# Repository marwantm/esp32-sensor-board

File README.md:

# ESP32 Sensor Board

A 4-layer ESP32-C3 IoT sensor board with onboard LiPo charging, SD storage, and a multi-sensor front end, designed in KiCad by following Tech Explorations' full board-development pipeline tutorial — my most advanced build yet, covering the complete flow from schematic to manufacturing and assembly.

## Overview

This board is built around the **ESP32-C3-WROOM-02**, a RISC-V Wi-Fi/BLE module, paired with a small sensor suite (environmental, audio, and light), onboard SPI flash, microSD storage, and a full LiPo battery charging path — a compact, self-contained IoT sensor node platform.

| | |
|---|---|
| **MCU** | ESP32-C3-WROOM-02 (RISC-V, Wi-Fi + BLE) |
| **Sensors** | BME280 (temperature/humidity/pressure), electret mic + MAX4466 amplifier, TEMT6000 ambient light sensor |
| **Storage** | W25Q32JVSSIQ SPI flash (32 Mbit) + microSD card slot |
| **Connectivity** | USB-C (via CP2102N USB-UART bridge), I2C header for OLED display, GPIO breakout |
| **Power** | USB-C (5V) or LiPo battery (JST connector), MCP73871 Li-ion/LiPo charge management, LM1117MPX-3.3 LDO |
| **Programming** | Auto-program circuit (DTR/RTS → EN/IO0 via BC817 transistors) — no manual boot/reset sequence needed |
| **PCB** | 4-layer |
| **Design Tool** | KiCad 9 |

## What I Learned

This project pushed further than my previous boards, moving from single-sheet schematics and simple 2-layer boards into a full multilayer design with manufacturing and assembly considerations built in from the start:

**Schematic Design**
- Multi-sheet hierarchical schematic structure, splitting the design into logical sub-sheets (USB/flash, sensors, user interface, power)
- Creating a custom KiCad component library for parts not available in the standard libraries, registered globally for reuse in future projects
- Designing a complete LiPo charging path around the MCP73871, including charge-status indication (charging/charged LEDs) and battery sense/thermistor handling

**PCB Layout**
- Working with a 4-layer stack-up and signal tuning across layers
- Zone fills across both available and non-available power planes, and understanding how that affects plane continuity and return paths
- Component placement and routing for mixed digital, analog (microphone/amp), and RF (Wi-Fi/BLE) sections on the same board

**Manufacturing & Assembly**
- Design for Manufacturability (DFM) checks using HQDFM (NextPCB)
- Generating centroid (pick-and-place) files for PCB assembly
- Thinking through the board as something meant to be assembled by a fab, not just etched and hand-soldered

## Gallery

| Schematic (Power & USB) | Schematic (ESP32, USB, Flash) |
|---|---|
|  |  |

| Schematic (Sensors) | Schematic (User Interface) |
|---|---|
|  |  |

| PCB Top | PCB Bottom |
|---|---|
|  |  |

| 3D Front | 3D Back |
|---|---|
|  |  |

## Repository Structure

```
ESP32-Sensor-Board/
├── README.md
├── Hardware/                        # Manufacturing-ready outputs
│   ├── ESP32 Sensor Board_Schematic.pdf
│   ├── ESP32 Sensor Board_PCB.pdf
│   ├── BOM.csv
│   └── Gerbers.zip
├── Images/                          # Renders and layer screenshots
│   ├── 3D_Back.png
│   ├── 3D_Front.png
│   ├── PCB_Bottom.png
│   ├── PCB_Top.png
│   ├── Schematic_Page_1.png
│   ├── Schematic_Page_2.png
│   ├── Schematic_Page_3.png
│   └── Schematic_Page_4.png
└── Source Files/                    # Full KiCad project (editable source)
    ├── Additional Components/       # Custom library (parts, footprints)
    ├── Esp32 Sensor Board.kicad_pcb
    ├── Esp32 Sensor Board.kicad_prl
    ├── Esp32 Sensor Board.kicad_pro
    ├── Esp32 Sensor Board.kicad_sch
    ├── esp32-c3-02.kicad_sch
    ├── sensors.kicad_sch
    ├── user_interface.kicad_sch
    └── fp-lib-table
```

## Credit

Built by following [Tech Explorations](https://www.linkedin.com/company/techexplorations/)'s ESP32 sensor board tutorial, which covers the complete pipeline from board specification through ordering and assembly. This project is a learning exercise, not an original design — full credit for the schematic architecture and design decisions goes to Tech Explorations' tutorial series.

## Author

**Marwan Tamer**
Electrical Power Engineering student, building toward Embedded Systems Engineering
[LinkedIn](https://www.linkedin.com/in/-marwan-tamer)

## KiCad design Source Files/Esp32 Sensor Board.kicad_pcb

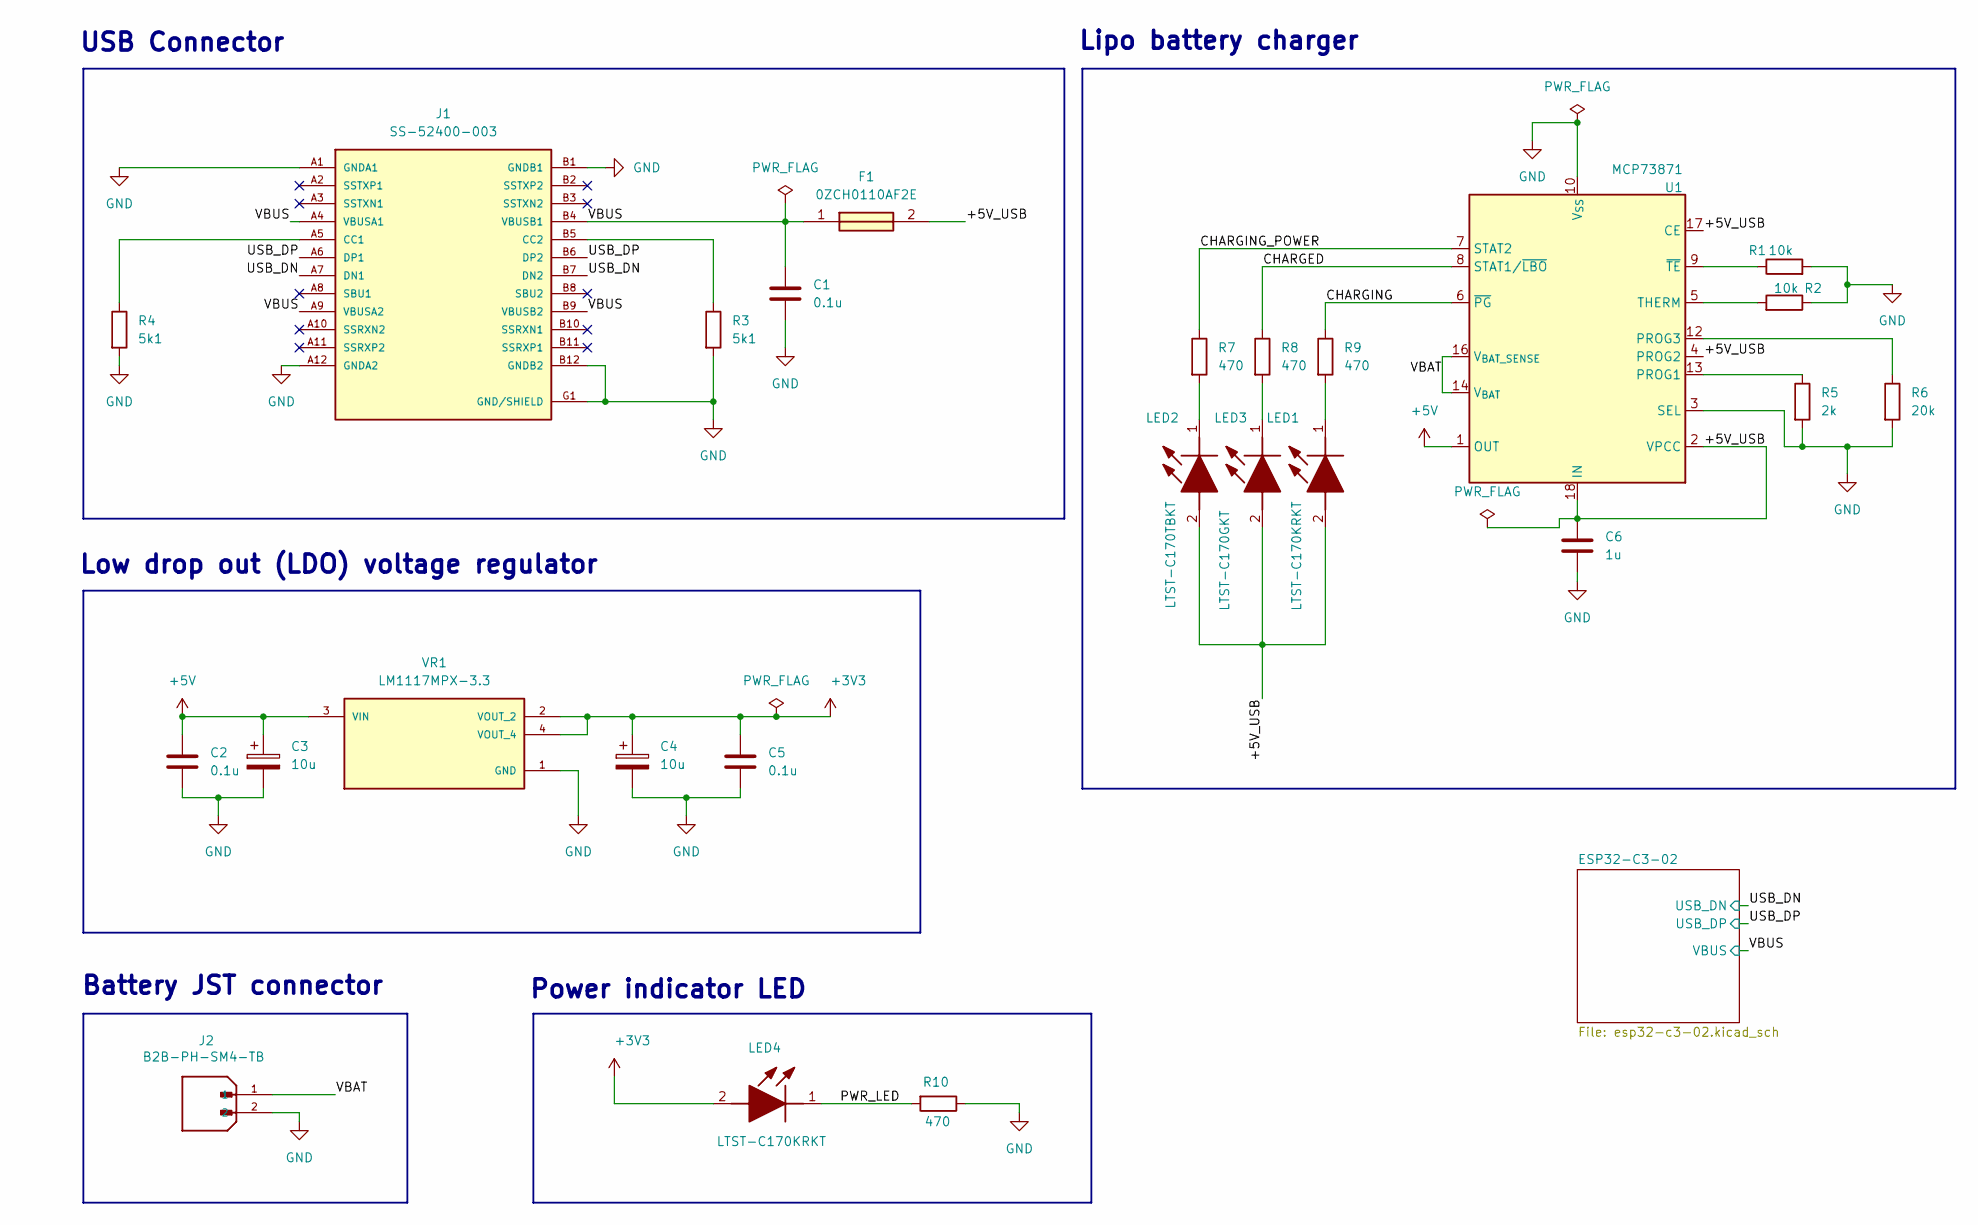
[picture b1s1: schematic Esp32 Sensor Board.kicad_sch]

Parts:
C1, C2, C5: 0.1u; C_0805_2012Metric
C3, C4: 10u; T491A
C6: 1u; C_0805_2012Metric
F1: 0ZCH0110AF2E; FUSC3226X100N; Manufacturer_Part_Number 0ZCH0110AF2E
J1: SS-52400-003; BELFUSE_SS-52400-003; PARTREV A0
J2: B2B-PH-SM4-TB; JST_B2B-PH-SM4-TB; PARTREV N/A
LED1, LED4: LTST-C170KRKT; LEDC2012X120N; Manufacturer_Part_Number LTST-C170KRKT; Mouser Part Number 859-LTST-C170KRKT
LED2: LTST-C170TBKT; LEDC2012X120N; Manufacturer_Part_Number LTST-C170TBKT; Mouser Part Number 859-LTST-C170TBKT
LED3: LTST-C170GKT; LEDC2012X120N; Manufacturer_Part_Number LTST-C170GKT; Mouser Part Number 859-LTST-C170GKT
R1, R2: 10k; R_0805_2012Metric
R3, R4: 5k1; R_0805_2012Metric
R5: 2k; R_0805_2012Metric
R6: 20k; R_0805_2012Metric
R7, R8, R9, R10: 470; R_0805_2012Metric
U1: MCP73871; QFN-20-1EP_4x4mm_P0.5mm_EP2.5x2.5mm
VR1: LM1117MPX-3.3; VREG_LM1117MPX-3.3

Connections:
+3V3: C4.1, C5.1, LED4.2 (A), VR1.2 (VOUT_2), VR1.4 (VOUT_4); also elsewhere on the board
+5V: C2.1, C3.1, U1.1 (OUT), U1.20 (OUT), VR1.3 (VIN)
/+5V_USB: C6.1, F1.2, LED1.2 (A), LED2.2 (A), LED3.2 (A), U1.2 (VPCC), U1.4 (PROG2), U1.17 (CE), U1.18 (IN), U1.19 (IN)
/CHARGED: R8.1, U1.8 (STAT1/~LBO)
/CHARGING: R9.1, U1.6 (~PG)
/CHARGING_POWER: R7.1, U1.7 (STAT2)
/PWR_LED: LED4.1 (K), R10.2
/USB_DN: J1.A7 (DN1), J1.B7 (DN2); also elsewhere on the board
/USB_DP: J1.A6 (DP1), J1.B6 (DP2); also elsewhere on the board
/VBAT: J2.1, U1.14 (V_{BAT}), U1.15 (V_{BAT}), U1.16 (V_{BAT_SENSE})
/VBUS: C1.1, F1.1, J1.A4 (VBUSA1), J1.A9 (VBUSA2), J1.B4 (VBUSB1), J1.B9 (VBUSB2); also elsewhere on the board
unnamed: J1.A5 (CC1), R4.1
unnamed: J1.B5 (CC2), R3.1
unnamed: LED1.1 (K), R9.2
unnamed: LED2.1 (K), R7.2
unnamed: LED3.1 (K), R8.2
unnamed: R5.1, U1.13 (PROG1)
unnamed: R6.1, U1.12 (PROG3)
unnamed: R1.1, U1.9 (~TE)

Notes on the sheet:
Lipo battery charger
Low drop out (LDO) voltage regulator
Battery JST connector
USB Connector
Power indicator LED

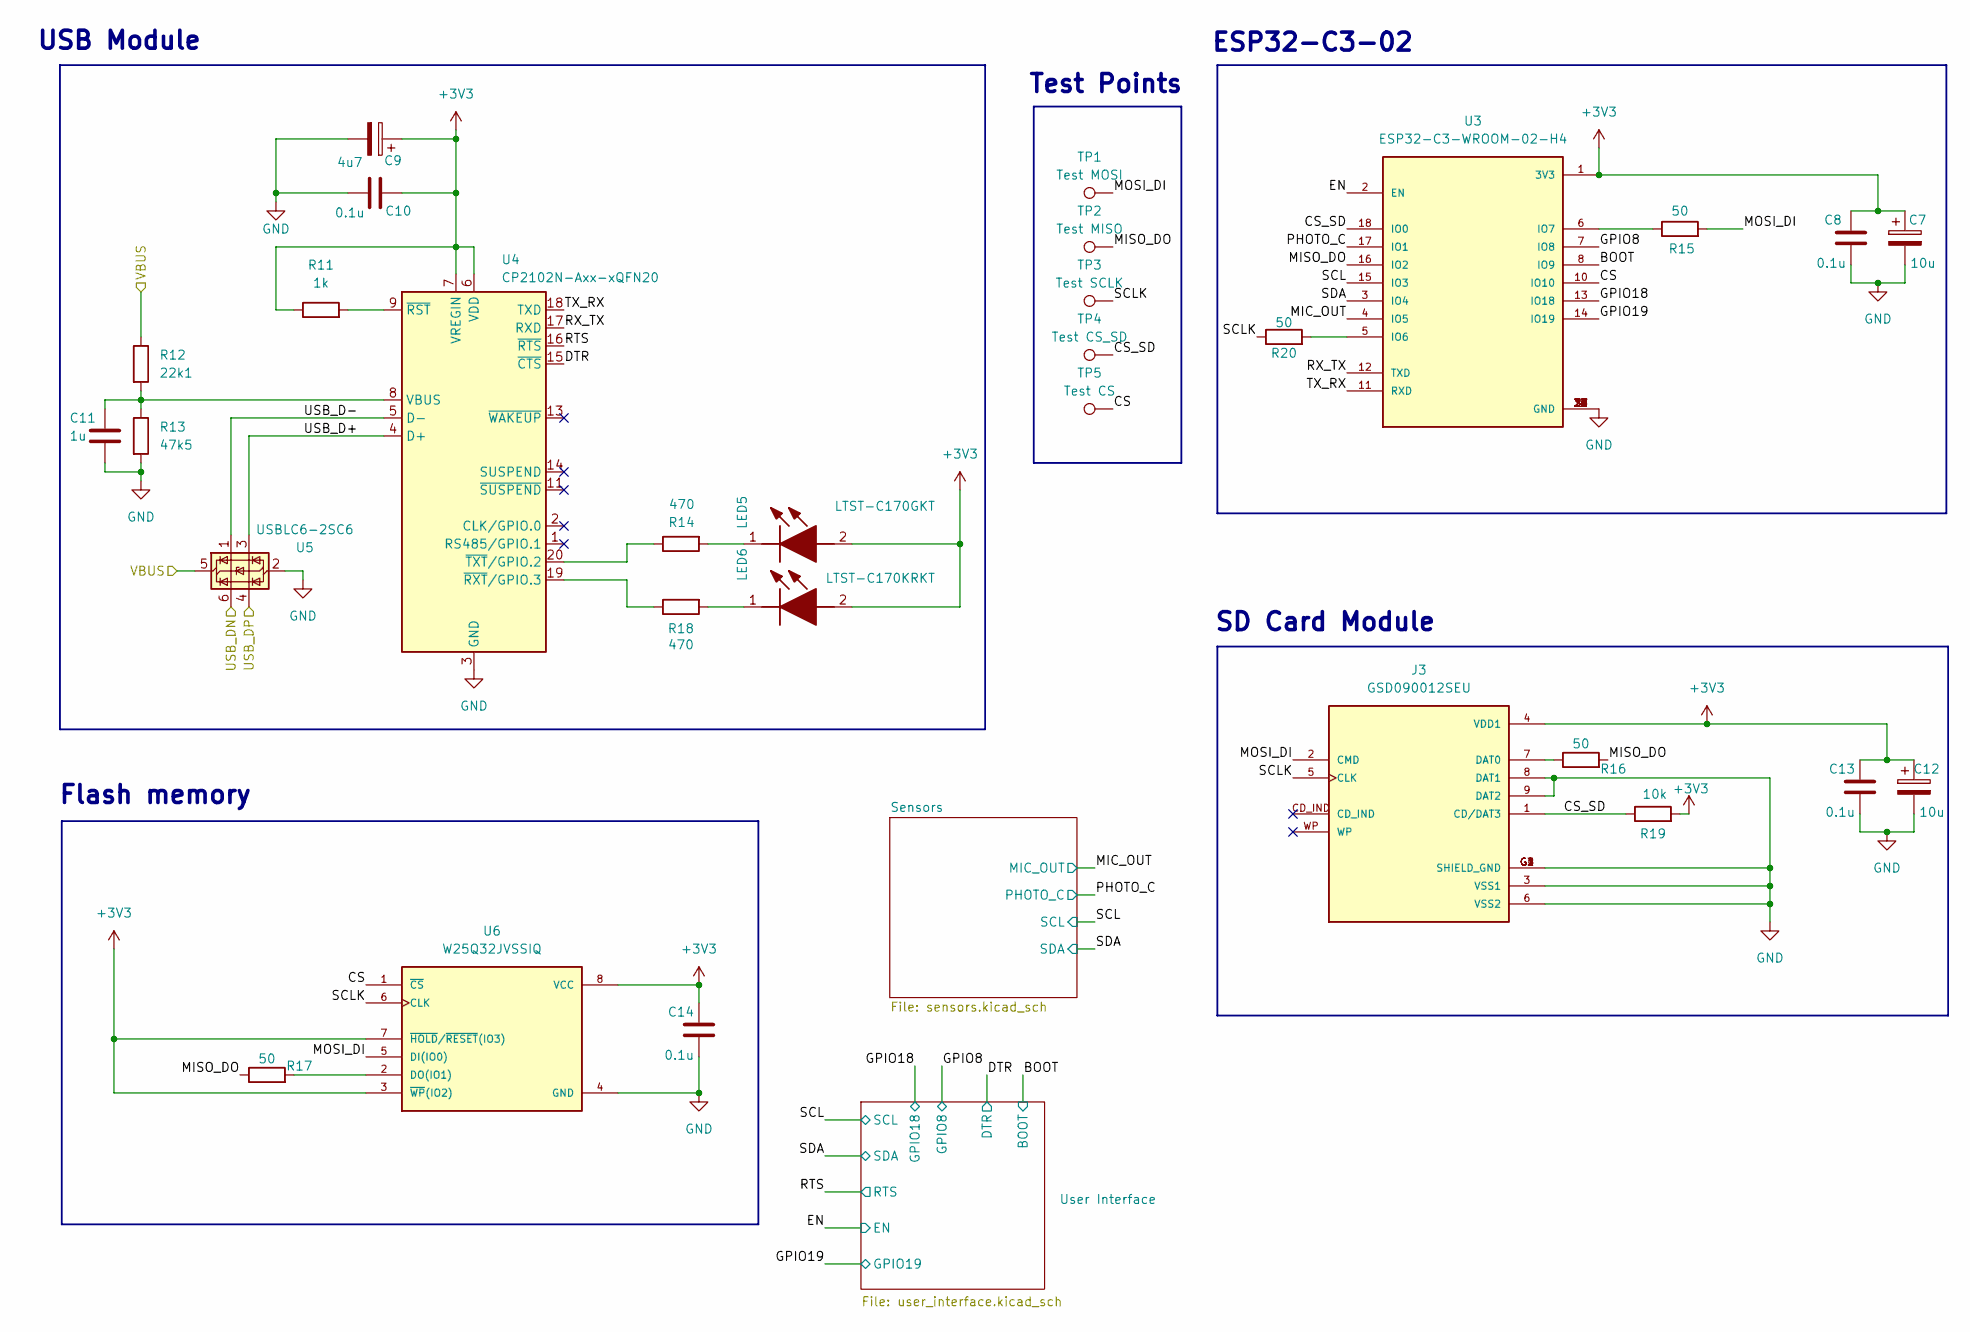
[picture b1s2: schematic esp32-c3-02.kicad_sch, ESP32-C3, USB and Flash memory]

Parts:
C7, C12: 10u; T491A
C8, C10, C13, C14: 0.1u; C_0805_2012Metric
C9: 4u7; T491A
C11: 1u; C_0805_2012Metric
J3: GSD090012SEU; AMPHENOL_GSD090012SEU; PARTREV E
LED5: LTST-C170GKT; LEDC2012X120N; Manufacturer_Part_Number LTST-C170GKT; Mouser Part Number 859-LTST-C170GKT
LED6: LTST-C170KRKT; LEDC2012X120N; Manufacturer_Part_Number LTST-C170KRKT; Mouser Part Number 859-LTST-C170KRKT
R11: 1k; R_0805_2012Metric
R12: 22k1; R_0805_2012Metric
R13: 47k5; R_0805_2012Metric
R14, R18: 470; R_0805_2012Metric
R15, R16, R17, R20: 50; R_0805_2012Metric
R19: 10k; R_0805_2012Metric
TP1: Test MOSI; TestPoint_Pad_D1.0mm
TP2: Test MISO; TestPoint_Pad_D1.0mm
TP3: Test SCLK; TestPoint_Pad_D1.0mm
TP4: Test CS_SD; TestPoint_Pad_D1.0mm
TP5: Test CS; TestPoint_Pad_D1.0mm
U3: ESP32-C3-WROOM-02-H4; MODULE_ESP32-C3-WROOM-02-H4
U4: CP2102N-Axx-xQFN20; SiliconLabs_QFN-20-1EP_3x3mm_P0.5mm_EP1.8x1.8mm
U5: USBLC6-2SC6; SOT-23-6
U6: W25Q32JVSSIQ; SOIC127P790X216-8N; M_PART_NUMBER W25QXX

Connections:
+3V3: C7.1, C8.2, C9.1, C10.2, C12.1, C13.2, C14.2, J3.4 (VDD1), LED5.2 (A), LED6.2 (A), R11.1, R19.2, U3.1 (3V3), U4.6 (VDD), U4.7 (VREGIN), U6.3 (~WP(IO2)), U6.7 (~HOLD/~RESET(IO3)), U6.8 (VCC); also elsewhere on the board
/ESP32-C3-02/BOOT: U3.8 (IO9); also elsewhere on the board
/ESP32-C3-02/CS: TP5.1, U3.10 (IO10), U6.1 (~CS)
/ESP32-C3-02/CS_SD: J3.1 (CD/DAT3), R19.1, TP4.1, U3.18 (IO0)
/ESP32-C3-02/DTR: U4.15 (~CTS); also elsewhere on the board
/ESP32-C3-02/EN: U3.2 (EN); also elsewhere on the board
/ESP32-C3-02/GPIO8: U3.7 (IO8); also elsewhere on the board
/ESP32-C3-02/GPIO18: U3.13 (IO18); also elsewhere on the board
/ESP32-C3-02/GPIO19: U3.14 (IO19); also elsewhere on the board
/ESP32-C3-02/MIC_OUT: U3.4 (IO5); also elsewhere on the board
/ESP32-C3-02/MISO_DO: R16.2, R17.1, TP2.1, U3.16 (IO2)
/ESP32-C3-02/MOSI_DI: J3.2 (CMD), R15.2, TP1.1, U6.5 (DI(IO0))
/ESP32-C3-02/PHOTO_C: U3.17 (IO1); also elsewhere on the board
/ESP32-C3-02/RTS: U4.16 (~RTS); also elsewhere on the board
/ESP32-C3-02/RX_TX: U3.12 (TXD), U4.17 (RXD)
/ESP32-C3-02/SCL: U3.15 (IO3); also elsewhere on the board
/ESP32-C3-02/SCLK: J3.5 (CLK), R20.1, TP3.1, U6.6 (CLK)
/ESP32-C3-02/SDA: U3.3 (IO4); also elsewhere on the board
/ESP32-C3-02/TX_RX: U3.11 (RXD), U4.18 (TXD)
/ESP32-C3-02/USB_D+: U4.4 (D+), U5.3 (I/O2)
/ESP32-C3-02/USB_D-: U4.5 (D-), U5.1 (I/O1)
/USB_DN: U5.6 (I/O1); also elsewhere on the board
/USB_DP: U5.4 (I/O2); also elsewhere on the board
/VBUS: R12.1, U5.5 (VBUS); also elsewhere on the board
unnamed: J3.7 (DAT0), R16.1
unnamed: LED5.1 (K), R14.2
unnamed: LED6.1 (K), R18.2
unnamed: R20.2, U3.5 (IO6)
unnamed: R15.1, U3.6 (IO7)
unnamed: C11.1, R12.2, R13.1, U4.8 (VBUS)
unnamed: R11.2, U4.9 (~RST)
unnamed: R18.1, U4.19 (~RXT/GPIO.3)
unnamed: R14.1, U4.20 (~TXT/GPIO.2)
unnamed: R17.2, U6.2 (DO(IO1))

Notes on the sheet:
USB Module
Test Points
SD Card Module
Flash memory
ESP32-C3-02

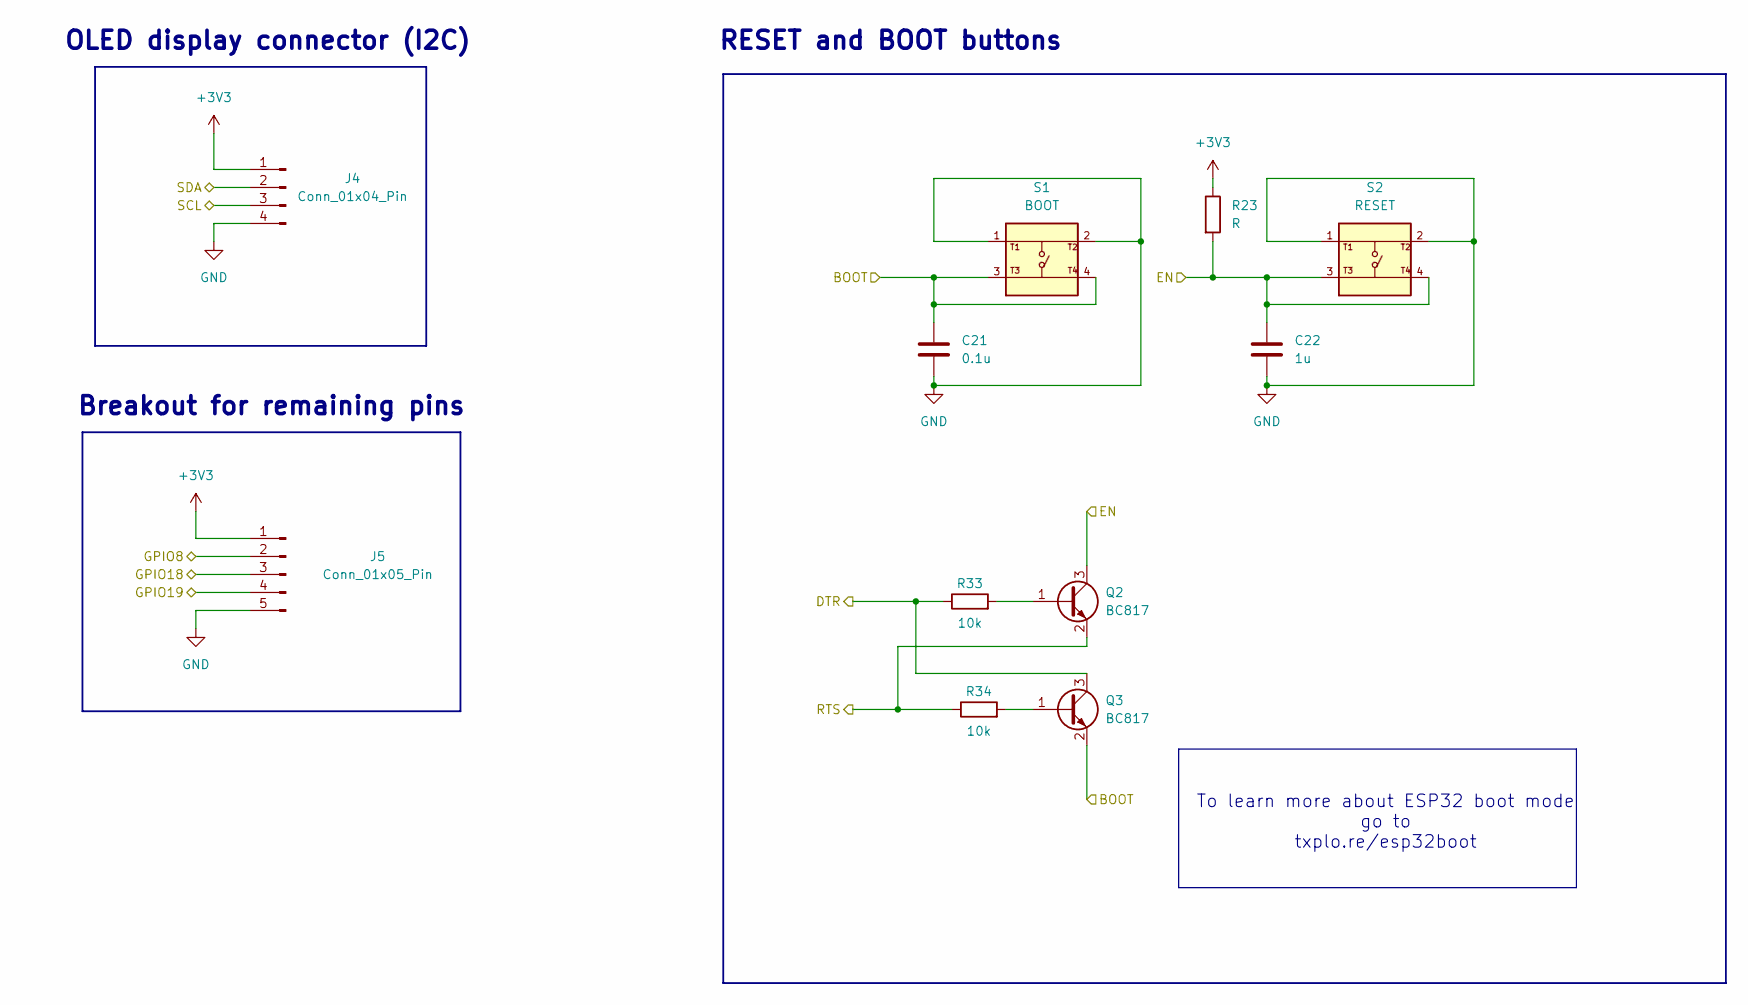
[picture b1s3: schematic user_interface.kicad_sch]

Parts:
C21: 0.1u; C_0805_2012Metric
C22: 1u; C_0805_2012Metric
J4: Conn_01x04_Pin; PinHeader_1x04_P2.54mm_Vertical
J5: Conn_01x05_Pin; PinHeader_1x05_P2.54mm_Vertical
Q2, Q3: BC817; SOT-23
R23: R; R_0805_2012Metric
R33, R34: 10k; R_0805_2012Metric
S1: BOOT; SW_USLPT2819DT2TR; PARTREV P
S2: RESET; SW_USLPT2819DT2TR; PARTREV P

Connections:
+3V3: J4.1, J5.1, R23.1; also elsewhere on the board
/ESP32-C3-02/BOOT: C21.1, Q3.2 (E), S1.3, S1.4; also elsewhere on the board
/ESP32-C3-02/DTR: Q3.3 (C), R33.1; also elsewhere on the board
/ESP32-C3-02/EN: C22.1, Q2.3 (C), R23.2, S2.3, S2.4; also elsewhere on the board
/ESP32-C3-02/GPIO8: J5.2; also elsewhere on the board
/ESP32-C3-02/GPIO18: J5.3; also elsewhere on the board
/ESP32-C3-02/GPIO19: J5.4; also elsewhere on the board
/ESP32-C3-02/RTS: Q2.2 (E), R34.1; also elsewhere on the board
/ESP32-C3-02/SCL: J4.3; also elsewhere on the board
/ESP32-C3-02/SDA: J4.2; also elsewhere on the board
unnamed: Q2.1 (B), R33.2
unnamed: Q3.1 (B), R34.2

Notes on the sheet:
Breakout for remaining pins
To learn more about ESP32 boot mode go to txplo.re/esp32boot
OLED display connector (I2C)
RESET and BOOT buttons

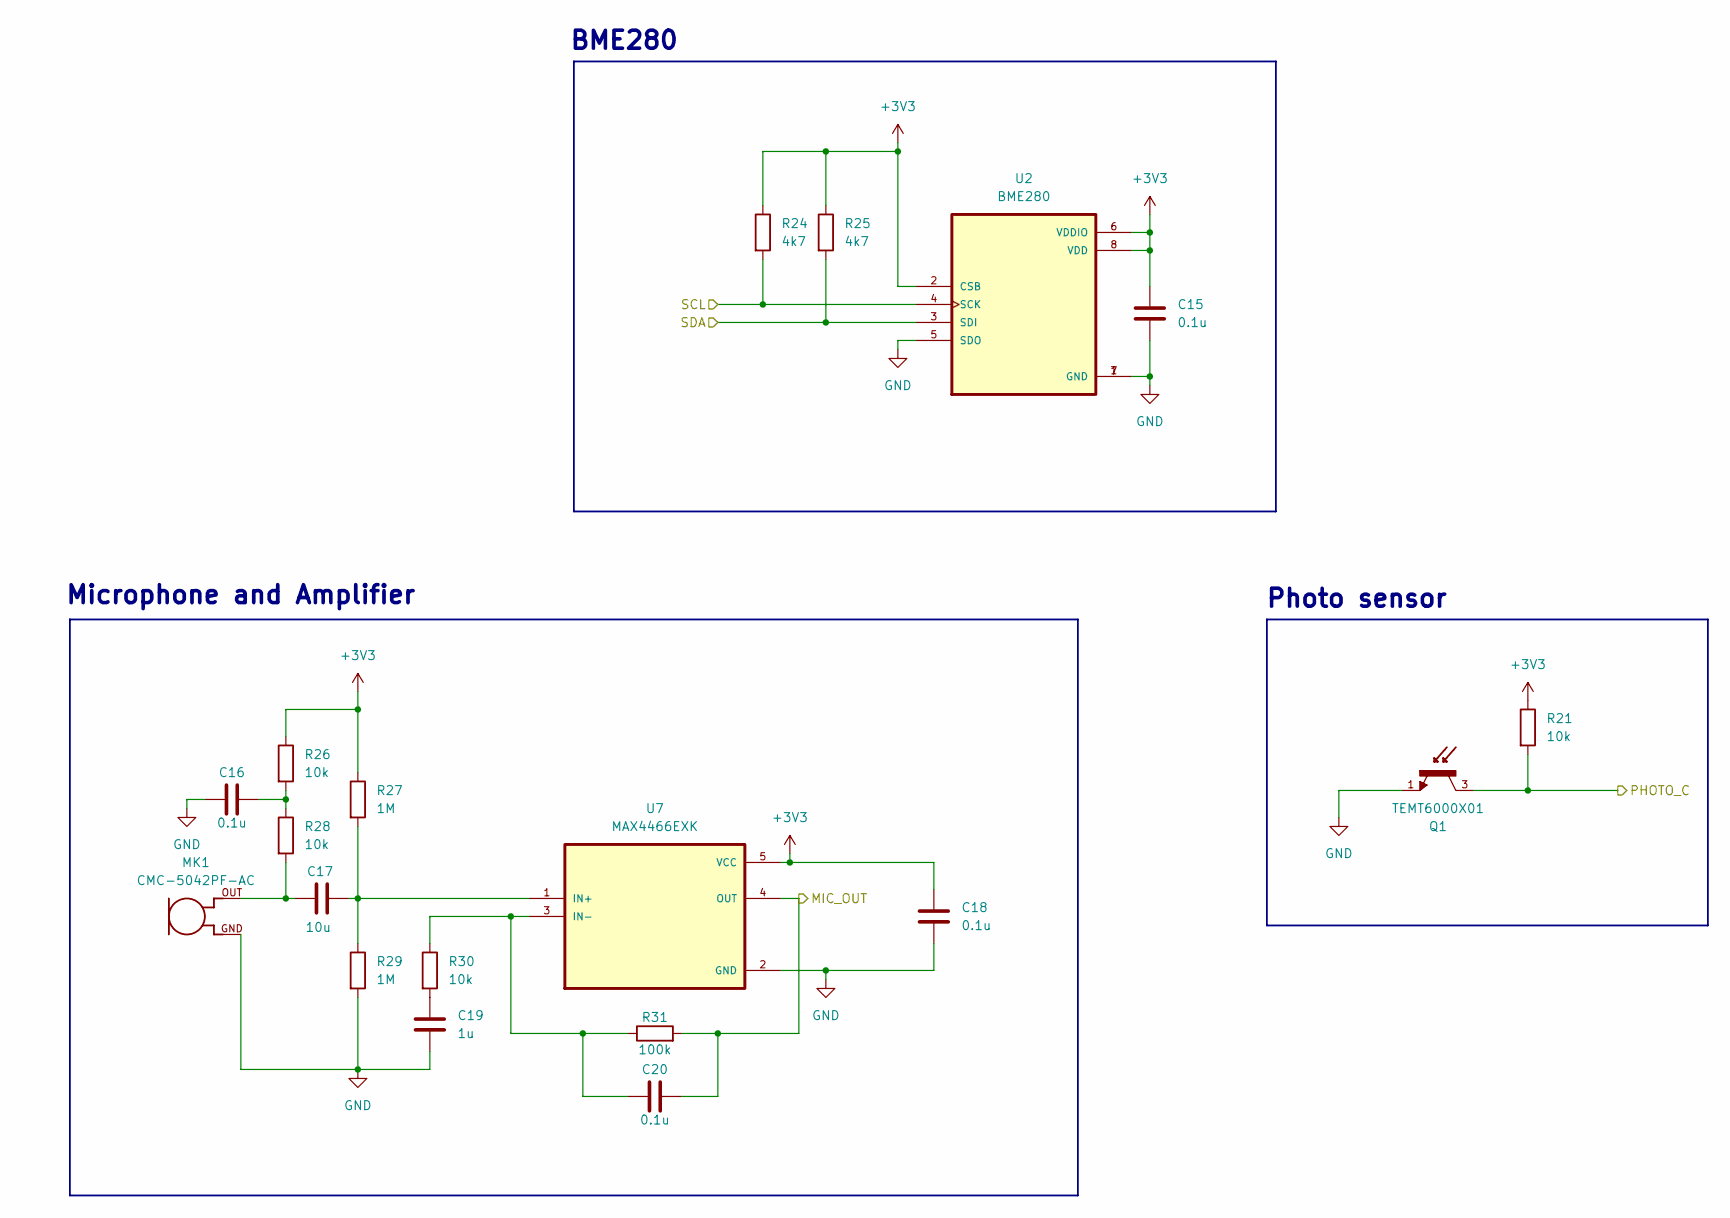
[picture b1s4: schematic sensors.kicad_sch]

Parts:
C15, C16, C18, C20: 0.1u; C_0805_2012Metric
C17: 10u; C_0805_2012Metric
C19: 1u; C_0805_2012Metric
MK1: CMC-5042PF-AC; CUI_CMC-5042PF-AC
Q1: TEMT6000X01; TRANS_TEMT6000X01; PARTREV 1.9
R21, R26, R28, R30: 10k; R_0805_2012Metric
R24, R25: 4k7; R_0805_2012Metric
R27, R29: 1M; R_0805_2012Metric
R31: 100k; R_0805_2012Metric
U2: BME280; PSON65P250X250X100-8N
U7: MAX4466EXK; SOT65P210X110-5N

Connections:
+3V3: C15.1, C18.1, R21.1, R24.1, R25.1, R26.1, R27.1, U2.2 (CSB), U2.6 (VDDIO), U2.8 (VDD), U7.5 (VCC); also elsewhere on the board
/ESP32-C3-02/MIC_OUT: C20.2, R31.2, U7.4 (OUT); also elsewhere on the board
/ESP32-C3-02/PHOTO_C: Q1.3, R21.2; also elsewhere on the board
/ESP32-C3-02/SCL: R24.2, U2.4 (SCK); also elsewhere on the board
/ESP32-C3-02/SDA: R25.2, U2.3 (SDI); also elsewhere on the board
unnamed: C16.2, R26.2, R28.1
unnamed: C17.1, MK1.OUT, R28.2
unnamed: C19.1, R30.2
unnamed: C17.2, R27.2, R29.1, U7.1 (IN+)
unnamed: C20.1, R30.1, R31.1, U7.3 (IN-)

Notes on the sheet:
Photo sensor
Microphone and Amplifier
BME280

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
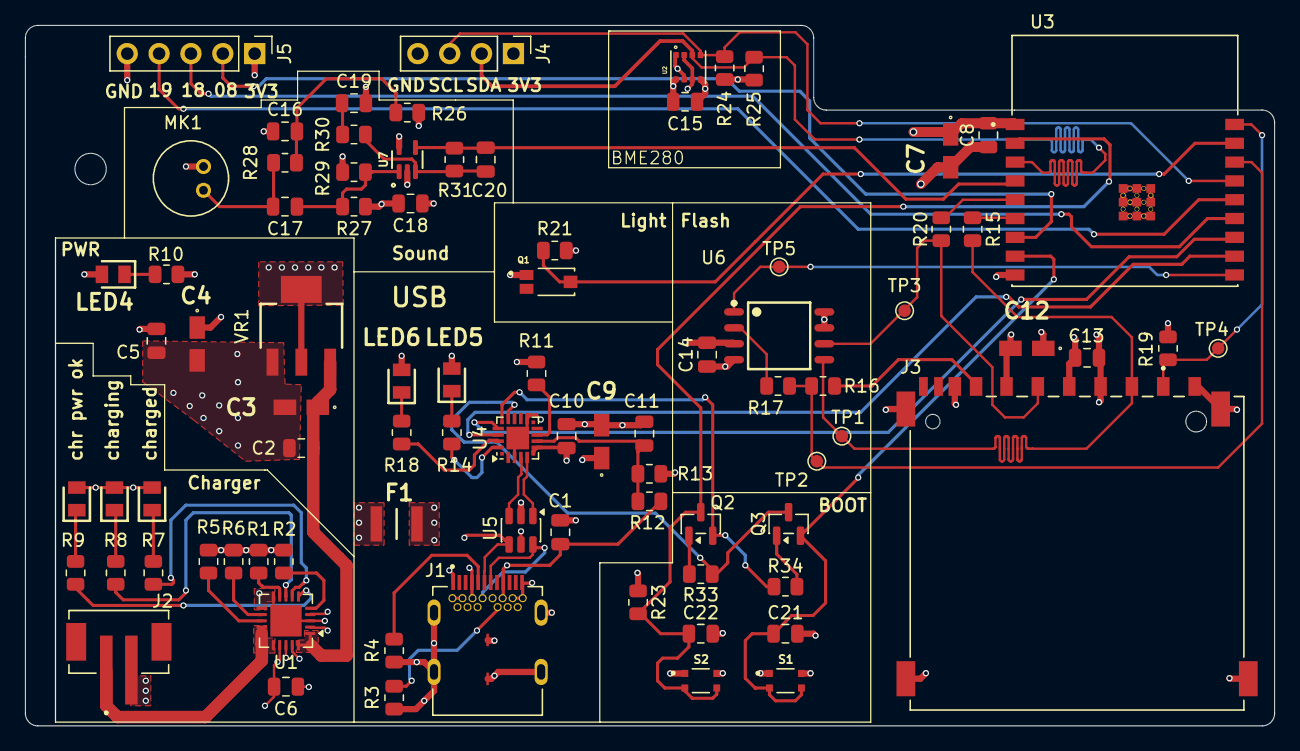
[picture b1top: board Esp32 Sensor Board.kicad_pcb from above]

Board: 4 copper layers, 99.6 x 55.8 mm, 85 parts (0 on the bottom side), 58 nets.

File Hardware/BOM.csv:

"Reference","Qty","Value","DNP","Exclude from BOM","Exclude from Board","Footprint","Datasheet"
"C1,C2,C5,C8,C10,C13,C14,C15,C16,C18,C20,C21","12","0.1u","","","","Capacitor_SMD:C_0805_2012Metric","~"
"C3,C4,C7,C12","4","10u","","","","My_Library:T491A","~"
"C6,C11,C19,C22","4","1u","","","","Capacitor_SMD:C_0805_2012Metric","~"
"C9","1","4u7","","","","My_Library:T491A","~"
"C17","1","10u","","","","Capacitor_SMD:C_0805_2012Metric","~"
"F1","1","0ZCH0110AF2E","","","","My_Library:FUSC3226X100N","https://www.belfuse.com/resources/datasheets/circuitprotecti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"
"J1","1","SS-52400-003","","","","My_Library:BELFUSE_SS-52400-003",""
"J2","1","B2B-PH-SM4-TB","","","","My_Library:JST_B2B-PH-SM4-TB",""
"J3","1","GSD090012SEU","","","","My_Library:AMPHENOL_GSD090012SEU",""
"J4","1","Conn_01x04_Pin","","","","Connector_PinHeader_2.54mm:PinHeader_1x04_P2.54mm_Vertical","~"
"J5","1","Conn_01x05_Pin","","","","Connector_PinHeader_2.54mm:PinHeader_1x05_P2.54mm_Vertical","~"
"LED1,LED4,LED6","3","LTST-C170KRKT","","","","My_Library:LEDC2012X120N","https://componentsearchengine.com/Datasheets/1/LTST-C170KRKT.pdf"
"LED2","1","LTST-C170TBKT","","","","My_Library:LEDC2012X120N","https://componentsearchengine.com/Datasheets/1/LTST-C170TBKT.pdf"
"LED3,LED5","2","LTST-C170GKT","","","","My_Library:LEDC2012X120N","https://mm.digikey.com/Volume0/opasdata/d220001/medias/docus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"
"MK1","1","CMC-5042PF-AC","","","","My_Library:CUI_CMC-5042PF-AC",""
"Q1","1","TEMT6000X01","","","","My_Library:TRANS_TEMT6000X01",""
"Q2,Q3","2","BC817","","","","Package_TO_SOT_SMD:SOT-23","https://www.onsemi.com/pub/Collateral/BC818-D.pdf"
"R1,R2,R19,R21,R26,R28,R30,R33,R34","9","10k","","","","Resistor_SMD:R_0805_2012Metric","~"
"R3,R4","2","5k1","","","","Resistor_SMD:R_0805_2012Metric","~"
"R5","1","2k","","","","Resistor_SMD:R_0805_2012Metric","~"
"R6","1","20k","","","","Resistor_SMD:R_0805_2012Metric","~"
"R7,R8,R9,R10,R14,R18","6","470","","","","Resistor_SMD:R_0805_2012Metric","~"
"R11","1","1k","","","","Resistor_SMD:R_0805_2012Metric","~"
"R12","1","22k1","","","","Resistor_SMD:R_0805_2012Metric","~"
"R13","1","47k5","","","","Resistor_SMD:R_0805_2012Metric","~"
"R15,R16,R17,R20","4","50","","","","Resistor_SMD:R_0805_2012Metric","~"
"R23","1","R","","","","Resistor_SMD:R_0805_2012Metric","~"
"R24,R25","2","4k7","","","","Resistor_SMD:R_0805_2012Metric","~"
"R27,R29","2","1M","","","","Resistor_SMD:R_0805_2012Metric","~"
"R31","1","100k","","","","Resistor_SMD:R_0805_2012Metric","~"
"S1","1","BOOT","","","","My_Library:SW_USLPT2819DT2TR",""
"S2","1","RESET","","","","My_Library:SW_USLPT2819DT2TR",""
"TP1","1","Test MOSI","","","","TestPoint:TestPoint_Pad_D1.0mm","~"
"TP2","1","Test MISO","","","","TestPoint:TestPoint_Pad_D1.0mm","~"
"TP3","1","Test SCLK","","","","TestPoint:TestPoint_Pad_D1.0mm","~"
"TP4","1","Test CS_SD","","","","TestPoint:TestPoint_Pad_D1.0mm","~"
"TP5","1","Test CS","","","","TestPoint:TestPoint_Pad_D1.0mm","~"
"U1","1","MCP73871","","","","Package_DFN_QFN:QFN-20-1EP_4x4mm_P0.5mm_EP2.5x2.5mm","http://www.mouser.com/ds/2/268/22090a-52174.pdf"
"U2","1","BME280","","","","My_Library:PSON65P250X250X100-8N",""
"U3","1","ESP32-C3-WROOM-02-H4","","","","My_Library:MODULE_ESP32-C3-WROOM-02-H4",""
"U4","1","CP2102N-Axx-xQFN20","","","","Package_DFN_QFN:SiliconLabs_QFN-20-1EP_3x3mm_P0.5mm_EP1.8x1.8mm","https://www.silabs.com/documents/public/data-sheets/cp2102n-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"
"U5","1","USBLC6-2SC6","","","","Package_TO_SOT_SMD:SOT-23-6","https://www.st.com/resource/en/datasheet/usblc6-2.pdf"
"U6","1","W25Q32JVSSIQ","","","","My_Library:SOIC127P790X216-8N",""
"U7","1","MAX4466EXK","","","","My_Library:SOT65P210X110-5N",""
"VR1","1","LM1117MPX-3.3","","","","My_Library:VREG_LM1117MPX-3.3",""
